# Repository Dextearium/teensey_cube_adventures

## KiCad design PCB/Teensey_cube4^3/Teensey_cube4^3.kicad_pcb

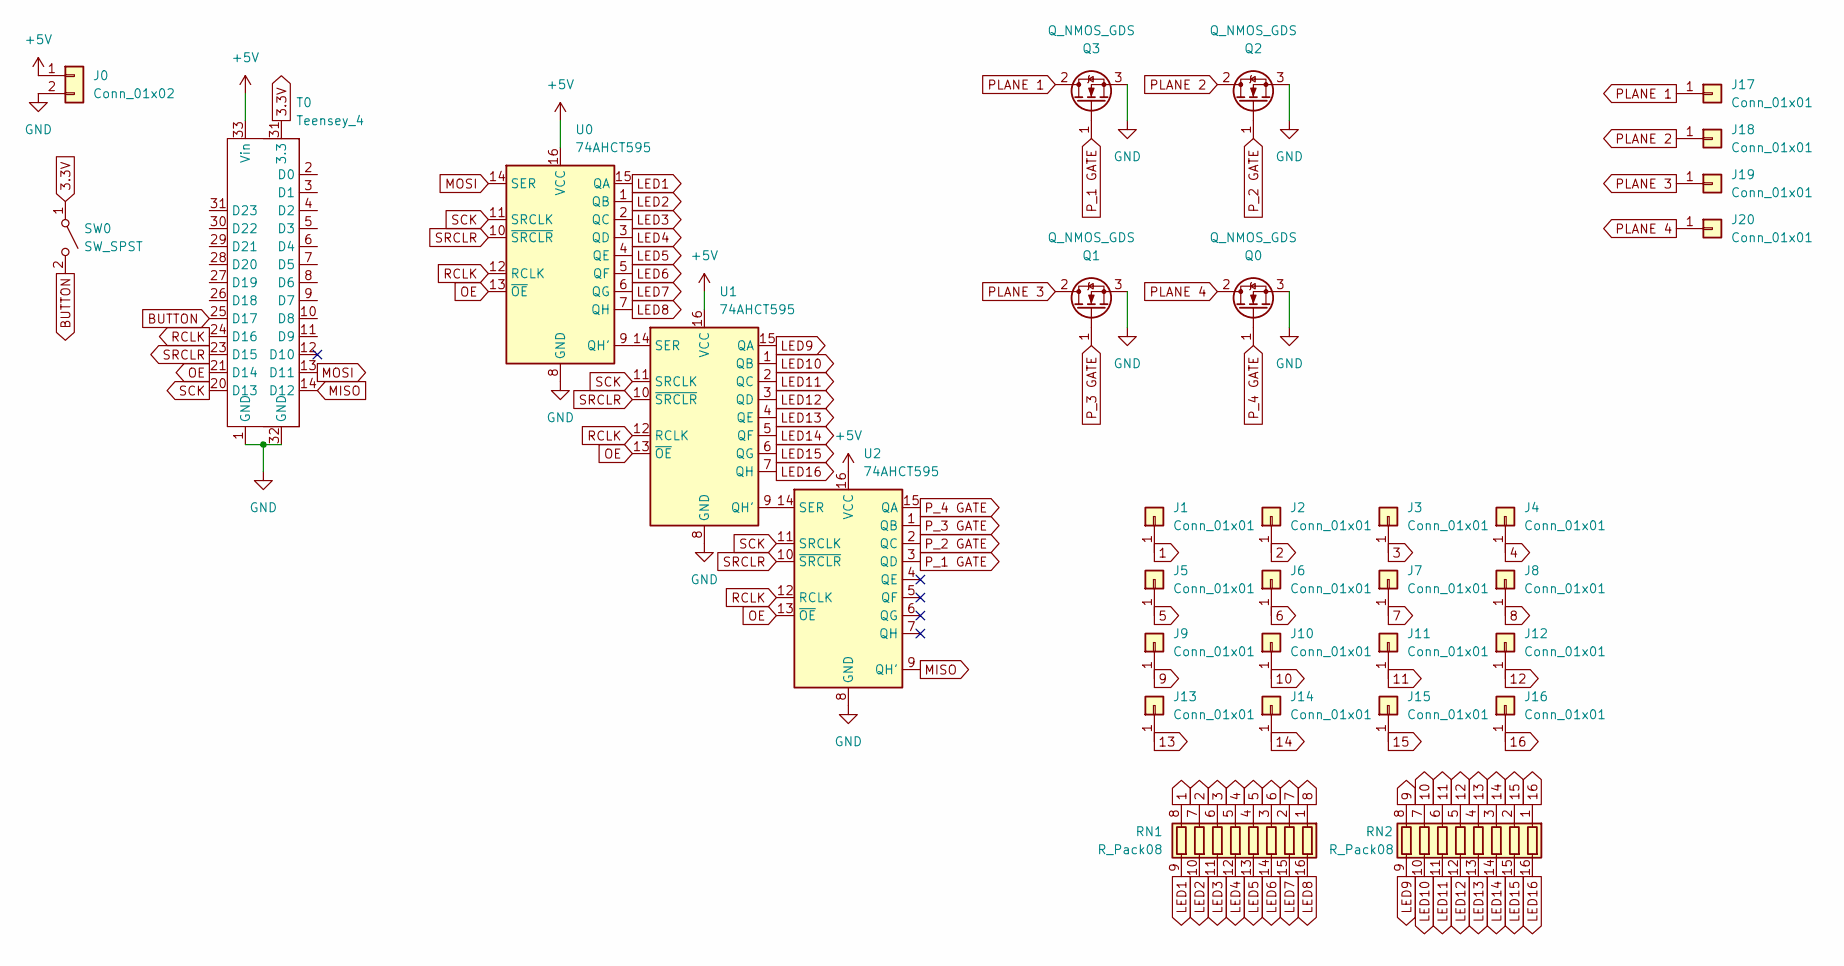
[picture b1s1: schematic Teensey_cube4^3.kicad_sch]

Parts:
J0: Conn_01x02; TE_826576-2_1x02_P3.96mm_Vertical
J1, J2, J3, J4, J5, J6, J7, J8, J9, J10, J11, J12, J13, J14, J15, J16, J17, J18, J19, J20: Conn_01x01; Pin_D1.0mm_L10.0mm
Q0, Q1, Q2, Q3: Q_NMOS_GDS; TO-252-2
RN1, RN2: R_Pack08; DIP-16_W7.62mm_Socket
SW0: SW_SPST; SW_Cherry_MX_1.00u_PCB
T0: Teensey_4; Teensy4.0
U0, U1, U2: 74AHCT595; DIP-16_W7.62mm_Socket

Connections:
1: J1.1, RN1.8 (R8.1)
2: J2.1, RN1.7 (R7.1)
3: J3.1, RN1.6 (R6.1)
3.3V: SW0.1 (A), T0.31 (3.3)
4: J4.1, RN1.5 (R5.1)
5: J5.1, RN1.4 (R4.1)
6: J6.1, RN1.3 (R3.1)
7: J7.1, RN1.2 (R2.1)
8: J8.1, RN1.1 (R1.1)
9: J9.1, RN2.8 (R8.1)
10: J10.1, RN2.7 (R7.1)
11: J11.1, RN2.6 (R6.1)
12: J12.1, RN2.5 (R5.1)
13: J13.1, RN2.4 (R4.1)
14: J14.1, RN2.3 (R3.1)
15: J15.1, RN2.2 (R2.1)
16: J16.1, RN2.1 (R1.1)
+5V: J0.1, T0.33 (Vin), U0.16 (VCC), U1.16 (VCC), U2.16 (VCC)
BUTTON: SW0.2 (B), T0.25 (D17)
GND: J0.2, Q0.3 (S), Q1.3 (S), Q2.3 (S), Q3.3 (S), T0.1 (GND), T0.32 (GND), U0.8 (GND), U1.8 (GND), U2.8 (GND)
LED1: RN1.9 (R8.2), U0.15 (QA)
LED2: RN1.10 (R7.2), U0.1 (QB)
LED3: RN1.11 (R6.2), U0.2 (QC)
LED4: RN1.12 (R5.2), U0.3 (QD)
LED5: RN1.13 (R4.2), U0.4 (QE)
LED6: RN1.14 (R3.2), U0.5 (QF)
LED7: RN1.15 (R2.2), U0.6 (QG)
LED8: RN1.16 (R1.2), U0.7 (QH)
LED9: RN2.9 (R8.2), U1.15 (QA)
LED10: RN2.10 (R7.2), U1.1 (QB)
LED11: RN2.11 (R6.2), U1.2 (QC)
LED12: RN2.12 (R5.2), U1.3 (QD)
LED13: RN2.13 (R4.2), U1.4 (QE)
LED14: RN2.14 (R3.2), U1.5 (QF)
LED15: RN2.15 (R2.2), U1.6 (QG)
LED16: RN2.16 (R1.2), U1.7 (QH)
MISO: T0.14 (D12), U2.9 (QH')
MOSI: T0.13 (D11), U0.14 (SER)
unnamed: U0.9 (QH'), U1.14 (SER)
unnamed: U1.9 (QH'), U2.14 (SER)
OE: T0.21 (D14), U0.13 (~OE), U1.13 (~OE), U2.13 (~OE)
PLANE 1: J17.1, Q3.2 (D)
PLANE 2: J18.1, Q2.2 (D)
PLANE 3: J19.1, Q1.2 (D)
PLANE 4: J20.1, Q0.2 (D)
P_1 GATE: Q3.1 (G), U2.3 (QD)
P_2 GATE: Q2.1 (G), U2.2 (QC)
P_3 GATE: Q1.1 (G), U2.1 (QB)
P_4 GATE: Q0.1 (G), U2.15 (QA)
RCLK: T0.24 (D16), U0.12 (RCLK), U1.12 (RCLK), U2.12 (RCLK)
SCK: T0.20 (D13), U0.11 (SRCLK), U1.11 (SRCLK), U2.11 (SRCLK)
SRCLR: T0.23 (D15), U0.10 (~SRCLR), U1.10 (~SRCLR), U2.10 (~SRCLR)

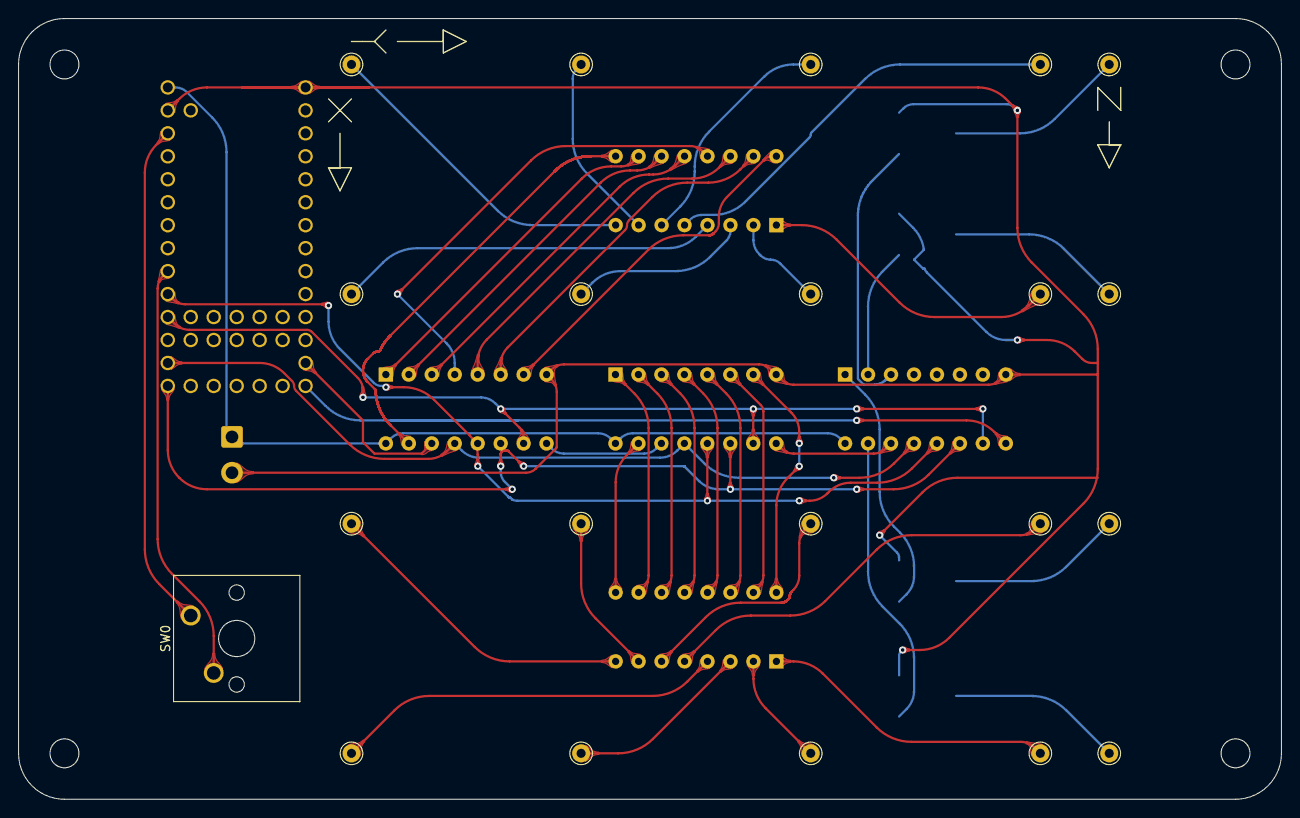
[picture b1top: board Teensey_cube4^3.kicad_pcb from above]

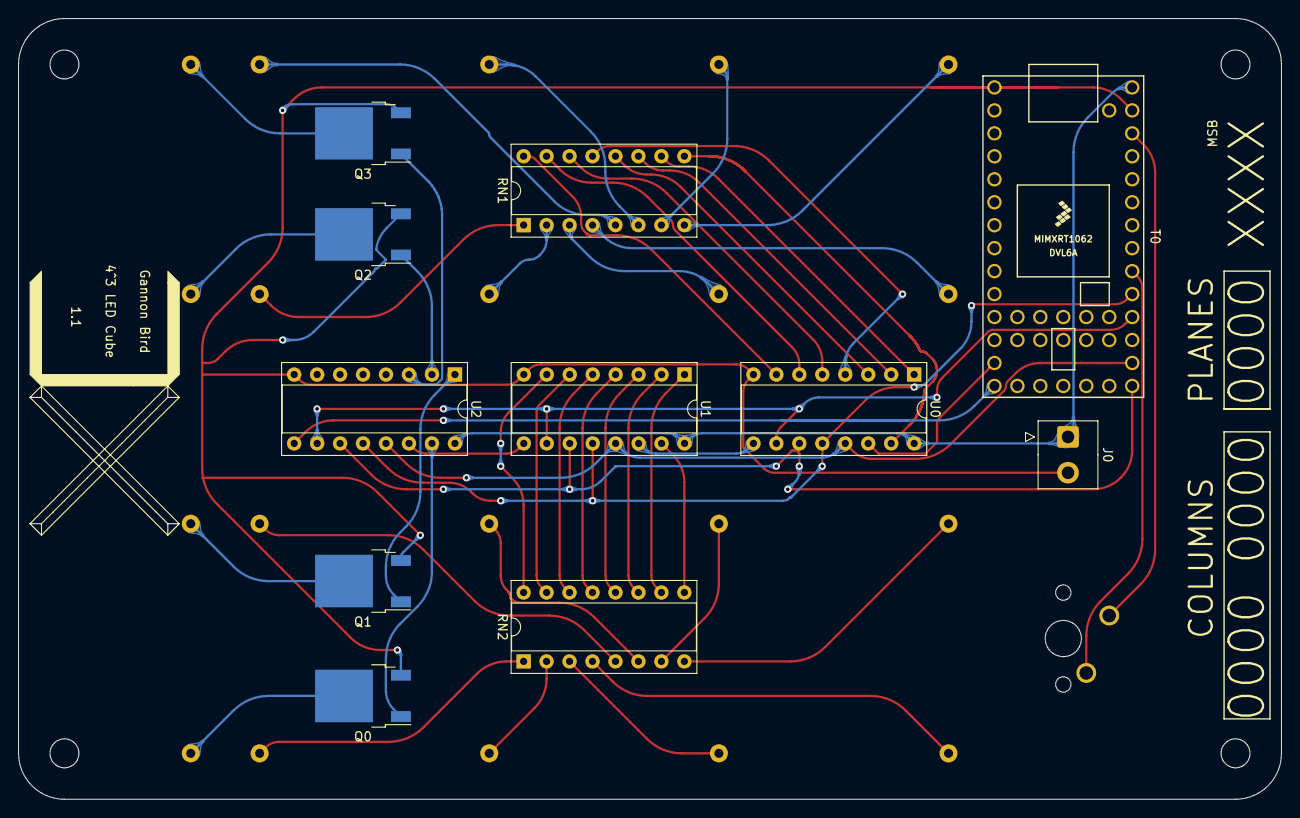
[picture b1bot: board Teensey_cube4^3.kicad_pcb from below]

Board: 2 copper layers, 139.7 x 86.4 mm, 32 parts (11 on the bottom side), 52 nets.

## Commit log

2022-06-22 added pcb files
2022-06-24 added 4^3 rgb pcb folder and stating files
2022-07-01 added the beginning of code
2022-07-01 completed cordinate system
2022-07-11 added brightness control
